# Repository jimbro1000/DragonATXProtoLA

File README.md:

# Dragon 32 ATX Prototype LA

This repository contains the KiCad project files
to produce logic analyser interface board for my
ATX Prototype backplane.

This design requires the ATX backplane board in order 
to operate
See https://github.com/jimbro1000/DragonATXProto

## Notes

The board requires the use of 5 Dr Gusman Pico
analyser boards.

This design has been completed using KiCad 9. Earlier
versions of KiCad are not compatible.

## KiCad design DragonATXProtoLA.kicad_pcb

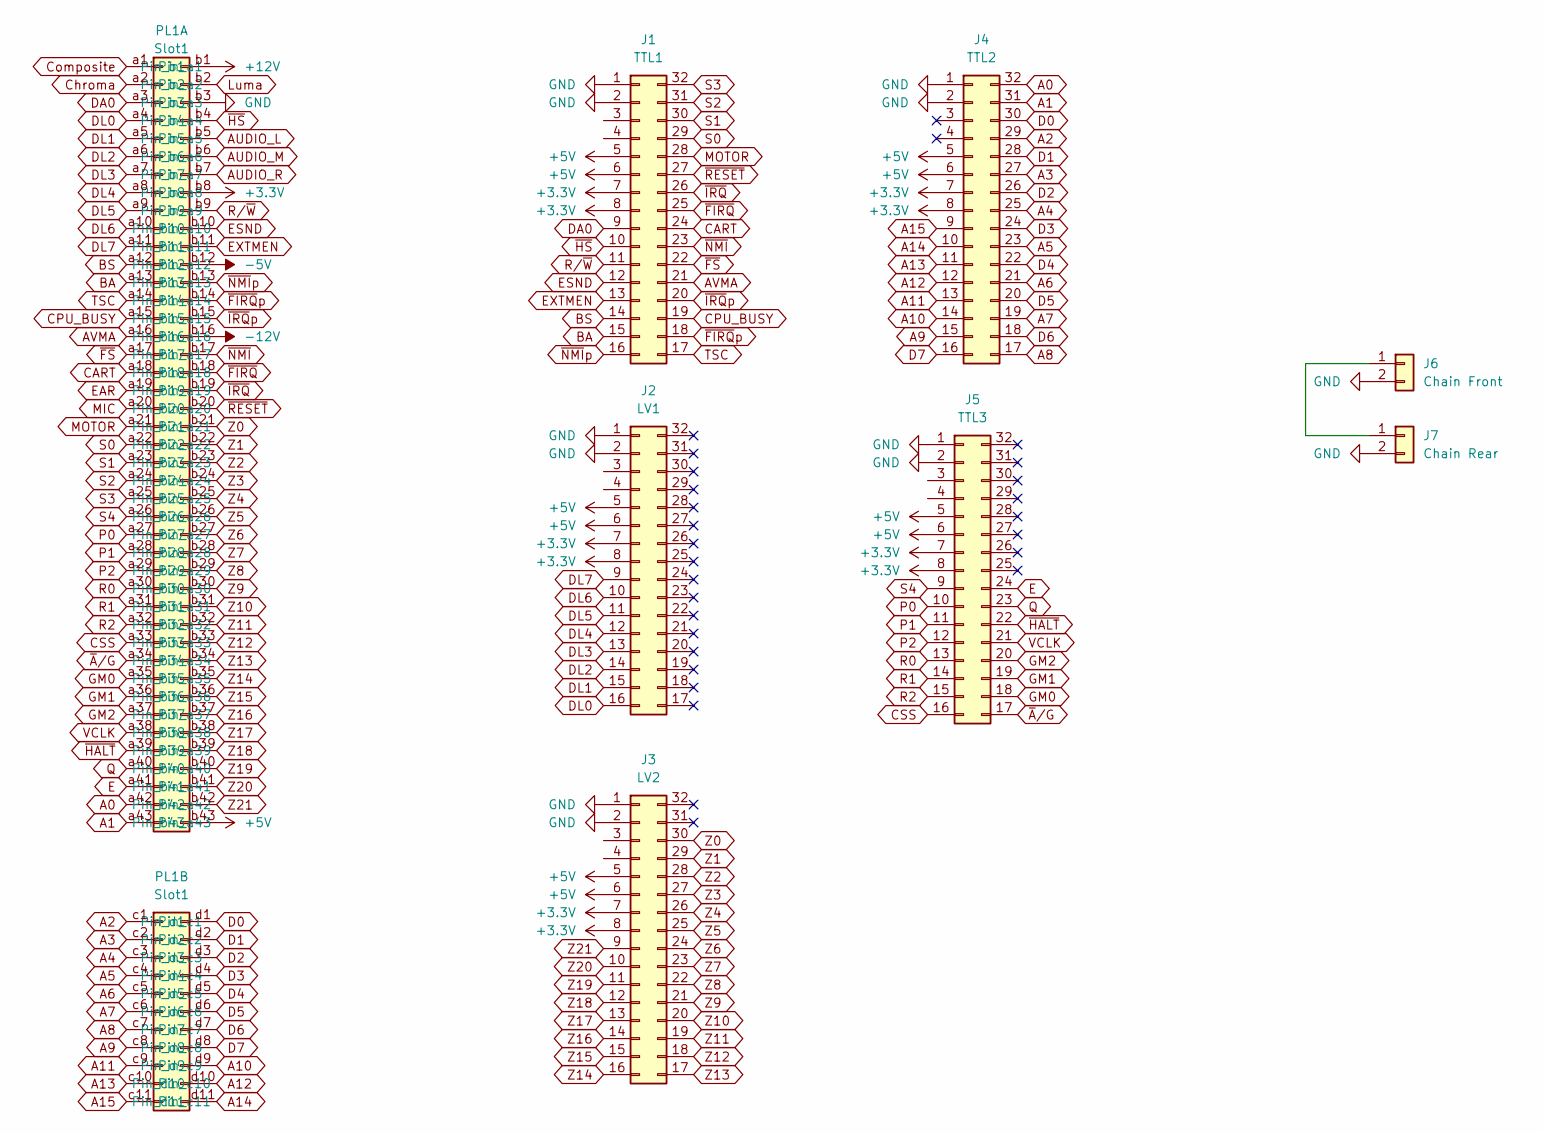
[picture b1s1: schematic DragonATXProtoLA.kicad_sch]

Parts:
J1: TTL1; PinSocket_2x16_P2.54mm_Horizontal
J2: LV1; PinSocket_2x16_P2.54mm_Horizontal
J3: LV2; PinSocket_2x16_P2.54mm_Horizontal
J4: TTL2; PinSocket_2x16_P2.54mm_Horizontal
J5: TTL3; PinSocket_2x16_P2.54mm_Horizontal
J6: Chain Front; PinSocket_1x02_P2.54mm_Horizontal
J7: Chain Rear; PinSocket_1x02_P2.54mm_Horizontal
PL1: Slot1; Card_Edge

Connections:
+3.3V: J1.7, J1.8, J2.7, J2.8, J3.7, J3.8, J4.7, J4.8, J5.7, J5.8, PL1.b8
+5V: J1.5, J1.6, J2.5, J2.6, J3.5, J3.6, J4.5, J4.6, J5.5, J5.6, PL1.b43
+12V: PL1.b1
-5V: PL1.b12
-12V: PL1.b16
A0: J4.32, PL1.a42
A1: J4.31, PL1.a43
A2: J4.29, PL1.c1
A3: J4.27, PL1.c2
A4: J4.25, PL1.c3
A5: J4.23, PL1.c4
A6: J4.21, PL1.c5
A7: J4.19, PL1.c6
A8: J4.17, PL1.c7
A9: J4.15, PL1.c8
A10: J4.14, PL1.d9
A11: J4.13, PL1.c9
A12: J4.12, PL1.d10
A13: J4.11, PL1.c10
A14: J4.10, PL1.d11
A15: J4.9, PL1.c11
AUDIO_L: PL1.b5
AUDIO_M: PL1.b6
AUDIO_R: PL1.b7
AVMA: J1.21, PL1.a16
BA: J1.15, PL1.a13
BS: J1.14, PL1.a12
CART: J1.24, PL1.a18
CPU_BUSY: J1.19, PL1.a15
CSS: J5.16, PL1.a33
Chroma: PL1.a2
Composite: PL1.a1
D0: J4.30, PL1.d1
D1: J4.28, PL1.d2
D2: J4.26, PL1.d3
D3: J4.24, PL1.d4
D4: J4.22, PL1.d5
D5: J4.20, PL1.d6
D6: J4.18, PL1.d7
D7: J4.16, PL1.d8
DA0: J1.9, PL1.a3
DL0: J2.16, PL1.a4
DL1: J2.15, PL1.a5
DL2: J2.14, PL1.a6
DL3: J2.13, PL1.a7
DL4: J2.12, PL1.a8
DL5: J2.11, PL1.a9
DL6: J2.10, PL1.a10
DL7: J2.9, PL1.a11
E: J5.24, PL1.a41
EAR: PL1.a19
ESND: J1.12, PL1.b10
EXTMEN: J1.13, PL1.b11
GM0: J5.18, PL1.a35
GM1: J5.19, PL1.a36
GM2: J5.20, PL1.a37
GND: J1.1, J1.2, J2.1, J2.2, J3.1, J3.2, J4.1, J4.2, J5.1, J5.2, J6.2, J7.2, PL1.b3
Luma: PL1.b2
MIC: PL1.a20
MOTOR: J1.28, PL1.a21
unnamed: J6.1, J7.1
P0: J5.10, PL1.a27
P1: J5.11, PL1.a28
P2: J5.12, PL1.a29
Q: J5.23, PL1.a40
R0: J5.13, PL1.a30
R1: J5.14, PL1.a31
R2: J5.15, PL1.a32
R/~W: J1.11, PL1.b9
S0: J1.29, PL1.a22
S1: J1.30, PL1.a23
S2: J1.31, PL1.a24
S3: J1.32, PL1.a25
S4: J5.9, PL1.a26
TSC: J1.17, PL1.a14
VCLK: J5.21, PL1.a38
Z0: J3.30, PL1.b21
Z1: J3.29, PL1.b22
Z2: J3.28, PL1.b23
Z3: J3.27, PL1.b24
Z4: J3.26, PL1.b25
Z5: J3.25, PL1.b26
Z6: J3.24, PL1.b27
Z7: J3.23, PL1.b28
Z8: J3.22, PL1.b29
Z9: J3.21, PL1.b30
Z10: J3.20, PL1.b31
Z11: J3.19, PL1.b32
Z12: J3.18, PL1.b33
Z13: J3.17, PL1.b34
Z14: J3.16, PL1.b35
Z15: J3.15, PL1.b36
Z16: J3.14, PL1.b37
Z17: J3.13, PL1.b38
Z18: J3.12, PL1.b39
Z19: J3.11, PL1.b40
Z20: J3.10, PL1.b41
Z21: J3.9, PL1.b42
~A/G: J5.17, PL1.a34
~FIRQ: J1.25, PL1.b18
~FIRQp: J1.18, PL1.b14
~FS: J1.22, PL1.a17
~HALT: J5.22, PL1.a39
~HS: J1.10, PL1.b4
~IRQ: J1.26, PL1.b19
~IRQp: J1.20, PL1.b15
~NMI: J1.23, PL1.b17
~NMIp: J1.16, PL1.b13
~RESET: J1.27, PL1.b20

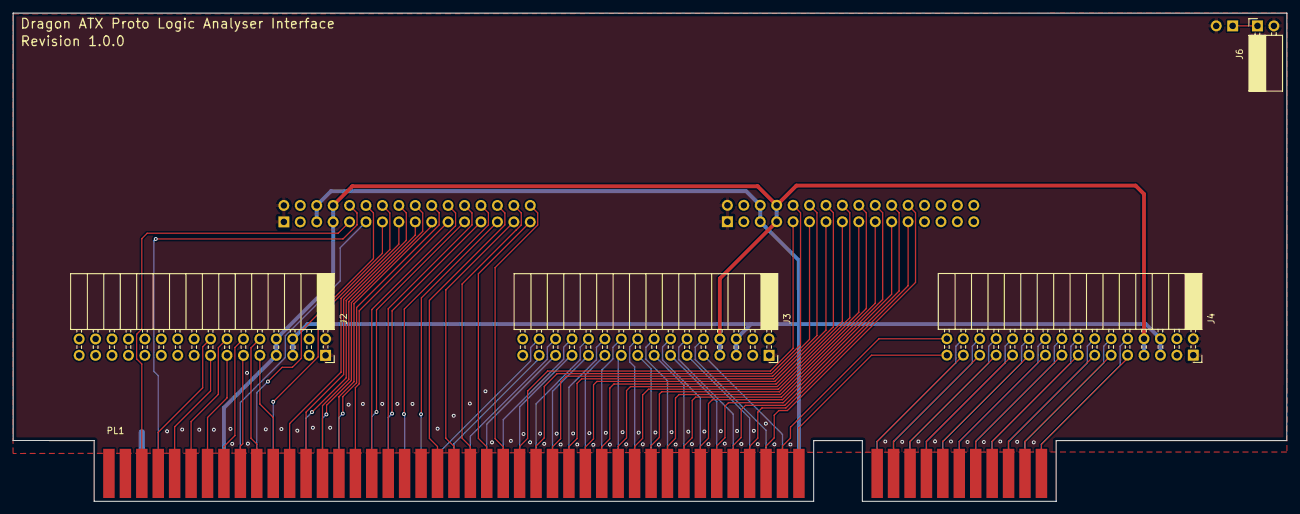
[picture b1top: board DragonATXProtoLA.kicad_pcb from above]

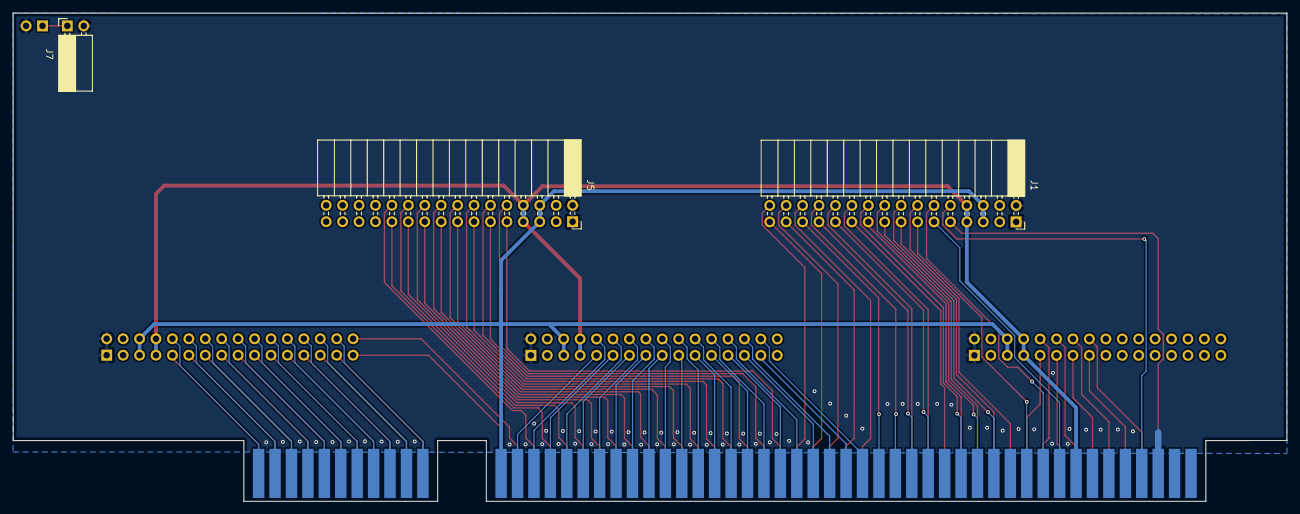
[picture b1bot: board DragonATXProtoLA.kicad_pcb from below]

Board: 2 copper layers, 197.0 x 75.5 mm, 8 parts (3 on the bottom side), 98 nets.

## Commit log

2025-03-02 add render of board
2025-03-18 upgrade card edge spec
2025-03-24 prepare for fabrication
